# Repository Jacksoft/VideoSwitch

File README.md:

# VideoSwitch
VideoSwitch sources (PIC + Schematic)
This project is a VideoSwitch for retro devices (that uses SCART/Composite) and is based on a mainboard composed by a PIC microcontroller, a main switch/selector and eight multiplexer, and a daughterboard (to be designed) to add eight more ports (up to two for a total of 24 inputs, not guaranteed until I'll produce a prototype for the right tests).
On the mainboard can be connected an 8x2 LCD character display (or biggher by modifying the firmware), two buttons for the input port selection and an IR receiver (not implemented yet firmware side, need to write the NEC IR library).
The firmware is in MikroBASIC (yes, I'm lazy and this language isn't the best for microcontrollers, I know).
Find out more on http://blog.jacksoftlabs.com/digital-video-switch-for-retro-devices/

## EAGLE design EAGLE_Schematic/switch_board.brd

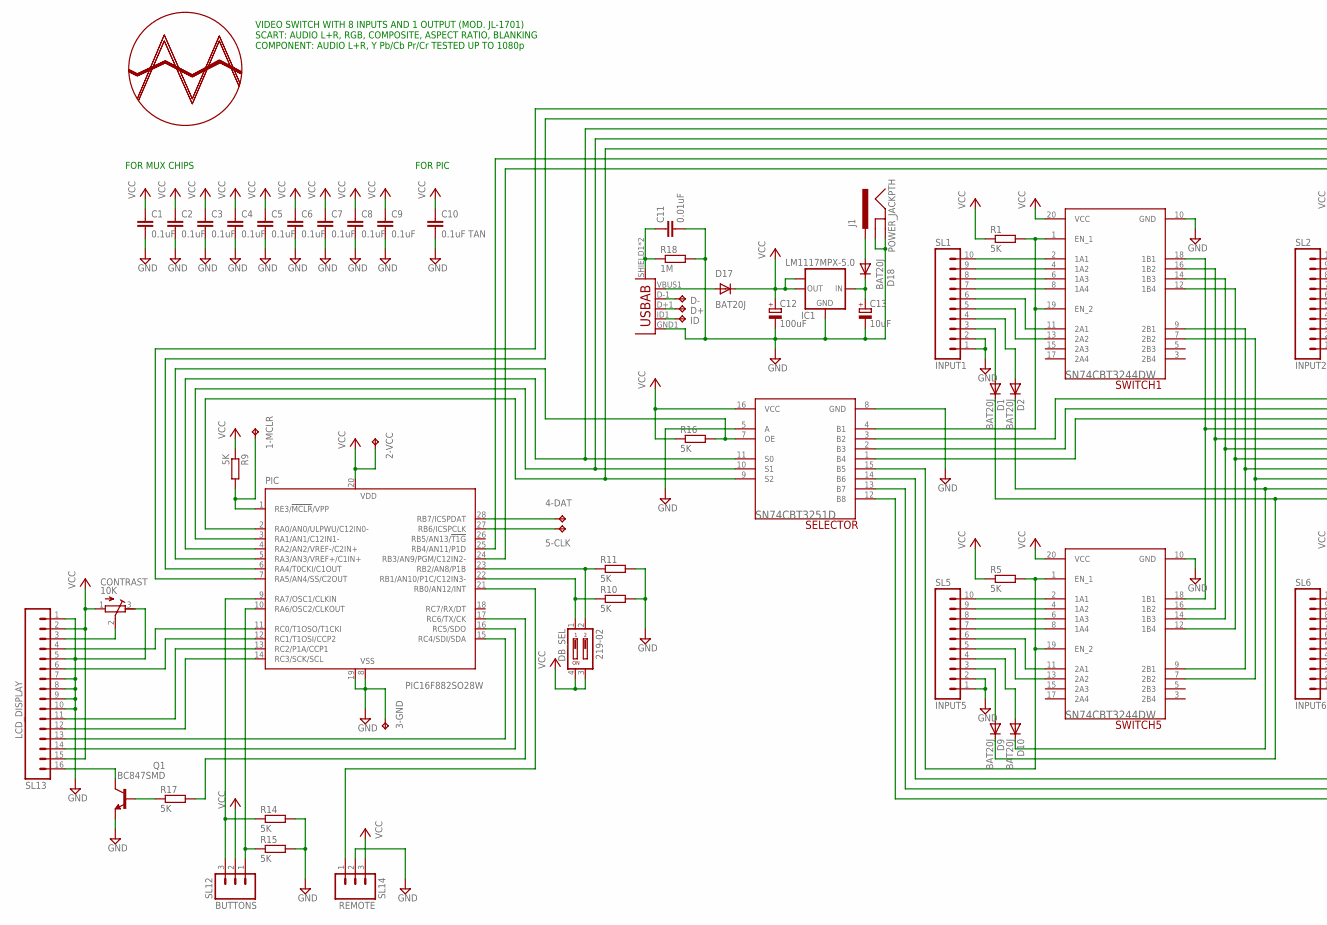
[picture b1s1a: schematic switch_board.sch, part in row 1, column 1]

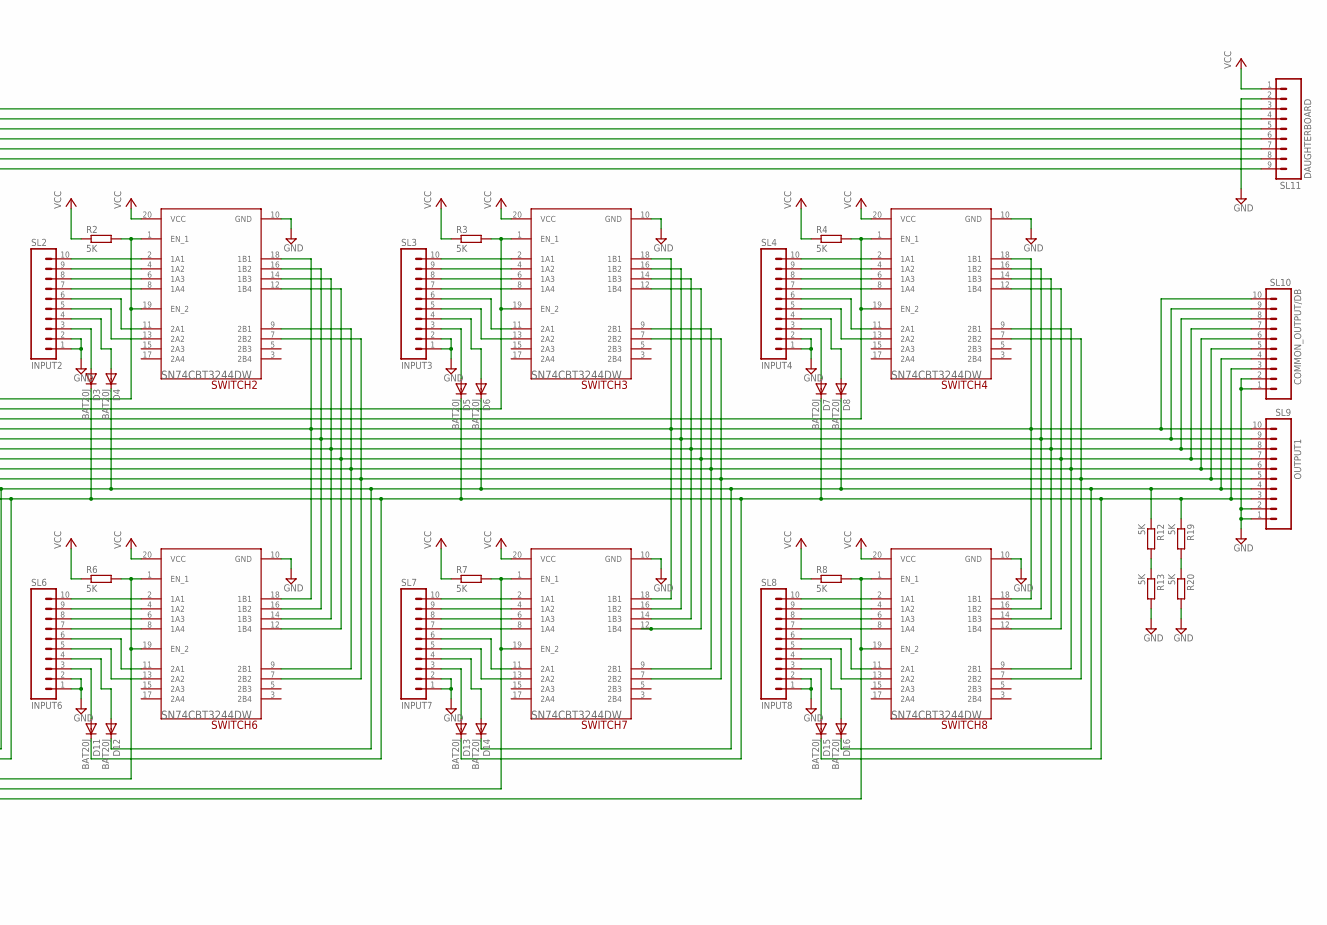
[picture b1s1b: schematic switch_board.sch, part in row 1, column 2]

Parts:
1-MCLR, 2-VCC, 3-GND, 4-DAT, 5-CLK: TPB1,27; B1,27
C1, C2, C3, C4, C5, C6, C7, C8, C9: 0.1uF; C0603
C10: 0.1uF TAN; C3216
C11: 0.01uF; C0603
C12: 100uF; 153CLV-0405
C13: 10uF; 153CLV-0405
CONTRAST: 10K; RTRIM3304W
D1, D2, D3, D4, D5, D6, D7, D8, D9, D10, D11, D12, D13, D14, D15, D16, D17, D18: BAT20J; SOD323-W
D+: TPTP06R; TP06R
D-: TPTP06R; TP06R
DB_SEL: 219-02; CTS-219-02
IC1: LM1117MPX-5.0; SOT223
ID: TPTP06R; TP06R
J1: POWER_JACKPTH; POWER_JACK_PTH
PIC: PIC16F882SO28W; 16F882
Q1: BC847SMD; SOT23
R1, R2, R3, R4, R5, R6, R7, R8, R9, R10, R11, R12, R13, R14, R15, R16, R17, R19, R20: 5K; R0603
R18: 1M; R0603
SELECTOR: SN74CBT3251D; SOIC127P1032X265-16N
SL1: INPUT1; 10P
SL2: INPUT2; 10P
SL3: INPUT3; 10P
SL4: INPUT4; 10P
SL5: INPUT5; 10P
SL6: INPUT6; 10P
SL7: INPUT7; 10P
SL8: INPUT8; 10P
SL9: OUTPUT1; 10P
SL10: COMMON_OUTPUT/DB; 10P
SL11: DAUGHTERBOARD; 09P
SL12: BUTTONS; 03P
SL13: LCD_DISPLAY; 16P
SL14: REMOTE; 03P
SWITCH1, SWITCH2, SWITCH3, SWITCH4, SWITCH5, SWITCH6, SWITCH7, SWITCH8: SN74CBT3244DW; SOIC127P1032X265-20N
U$1: JACKSOFTLABS-LOGOLONGTEXT; LOGO-LONGTEXT
USB: USB_POWER; USB-MICRO-SMD

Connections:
GND: 3-GND.TP, C1.2, C2.2, C3.2, C4.2, C5.2, C6.2, C7.2, C8.2, C9.2, C10.2, C11.2, C12.-, C13.-, CONTRAST.3 (E), IC1.1 (GND), J1.GND, J1.GNDBREAK, PIC.8 (VSS), PIC.19 (VSS), Q1.2 (E), R10.2, R11.2, R13.2, R14.2, R15.2, R18.2, R20.2, SELECTOR.5 (A), SELECTOR.8 (GND), SL1.1, SL1.2, SL2.1, SL2.2, SL3.1, SL3.2, SL4.1, SL4.2, SL5.1, SL5.2, SL6.1, SL6.2, SL7.1, SL7.2, SL8.1, SL8.2, SL9.1, SL9.2, SL10.1, SL10.2, SL11.2, SL13.1, SL13.5, SL13.7, SL13.8, SL13.9, SL13.10, SL14.2, SWITCH1.10 (GND), SWITCH2.10 (GND), SWITCH3.10 (GND), SWITCH4.10 (GND), SWITCH5.10 (GND), SWITCH6.10 (GND), SWITCH7.10 (GND), SWITCH8.10 (GND), USB.GND1 (GND)
unnamed: SL1.10, SWITCH1.2 (1A1)
unnamed: SL1.9, SWITCH1.4 (1A2)
unnamed: SL1.8, SWITCH1.6 (1A3)
unnamed: SL1.7, SWITCH1.8 (1A4)
unnamed: SL1.6, SWITCH1.11 (2A1)
unnamed: SL1.5, SWITCH1.13 (2A2)
unnamed: D2.A, SL1.4
unnamed: D1.A, SL1.3
unnamed: R1.2, SELECTOR.4 (B1), SWITCH1.1 (EN_1), SWITCH1.19 (EN_2)
unnamed: SL2.10, SWITCH2.2 (1A1)
unnamed: SL2.9, SWITCH2.4 (1A2)
unnamed: SL2.8, SWITCH2.6 (1A3)
unnamed: SL2.7, SWITCH2.8 (1A4)
unnamed: SL2.6, SWITCH2.11 (2A1)
unnamed: SL2.5, SWITCH2.13 (2A2)
unnamed: D4.A, SL2.4
unnamed: D3.A, SL2.3
unnamed: R2.2, SELECTOR.3 (B2), SWITCH2.1 (EN_1), SWITCH2.19 (EN_2)
unnamed: SL3.10, SWITCH3.2 (1A1)
unnamed: SL3.9, SWITCH3.4 (1A2)
unnamed: SL3.8, SWITCH3.6 (1A3)
unnamed: SL3.7, SWITCH3.8 (1A4)
unnamed: SL3.6, SWITCH3.11 (2A1)
unnamed: SL3.5, SWITCH3.13 (2A2)
unnamed: D6.A, SL3.4
unnamed: D5.A, SL3.3
unnamed: R3.2, SELECTOR.2 (B3), SWITCH3.1 (EN_1), SWITCH3.19 (EN_2)
unnamed: SL4.10, SWITCH4.2 (1A1)
unnamed: SL4.9, SWITCH4.4 (1A2)
unnamed: SL4.8, SWITCH4.6 (1A3)
unnamed: SL4.7, SWITCH4.8 (1A4)
unnamed: SL4.6, SWITCH4.11 (2A1)
unnamed: SL4.5, SWITCH4.13 (2A2)
unnamed: D8.A, SL4.4
unnamed: D7.A, SL4.3
unnamed: R4.2, SELECTOR.1 (B4), SWITCH4.1 (EN_1), SWITCH4.19 (EN_2)
unnamed: SL9.10, SL10.10, SWITCH1.18 (1B1), SWITCH2.18 (1B1), SWITCH3.18 (1B1), SWITCH4.18 (1B1), SWITCH5.18 (1B1), SWITCH6.18 (1B1), SWITCH7.18 (1B1), SWITCH8.18 (1B1)
unnamed: SL9.9, SL10.9, SWITCH1.16 (1B2), SWITCH2.16 (1B2), SWITCH3.16 (1B2), SWITCH4.16 (1B2), SWITCH5.16 (1B2), SWITCH6.16 (1B2), SWITCH7.16 (1B2), SWITCH8.16 (1B2)
unnamed: PIC.11 (RC0/T1OSO/T1CKI), SL13.4
unnamed: PIC.12 (RC1/T1OSI/CCP2), SL13.6
unnamed: PIC.13 (RC2/P1A/CCP1), SL13.11
unnamed: DB_SEL.1, PIC.22 (RB1/AN10/P1C/C12IN3-), R10.1
unnamed: PIC.14 (RC3/SCK/SCL), SL13.12
unnamed: CONTRAST.2 (S), SL13.3
unnamed: SL5.10, SWITCH5.2 (1A1)
unnamed: SL5.9, SWITCH5.4 (1A2)
unnamed: SL5.8, SWITCH5.6 (1A3)
unnamed: SL5.7, SWITCH5.8 (1A4)
unnamed: SL5.6, SWITCH5.11 (2A1)
unnamed: SL5.5, SWITCH5.13 (2A2)
unnamed: D10.A, SL5.4
unnamed: D9.A, SL5.3
unnamed: R5.2, SELECTOR.15 (B5), SWITCH5.1 (EN_1), SWITCH5.19 (EN_2)
unnamed: SL6.10, SWITCH6.2 (1A1)
unnamed: SL6.9, SWITCH6.4 (1A2)
unnamed: SL6.8, SWITCH6.6 (1A3)
unnamed: SL6.7, SWITCH6.8 (1A4)
unnamed: SL6.6, SWITCH6.11 (2A1)
unnamed: SL6.5, SWITCH6.13 (2A2)
unnamed: D12.A, SL6.4
unnamed: D11.A, SL6.3
unnamed: R6.2, SELECTOR.14 (B6), SWITCH6.1 (EN_1), SWITCH6.19 (EN_2)
unnamed: SL7.10, SWITCH7.2 (1A1)
unnamed: SL7.9, SWITCH7.4 (1A2)
unnamed: SL7.8, SWITCH7.6 (1A3)
unnamed: SL7.7, SWITCH7.8 (1A4)
unnamed: SL7.6, SWITCH7.11 (2A1)
unnamed: SL7.5, SWITCH7.13 (2A2)
unnamed: D14.A, SL7.4
unnamed: D13.A, SL7.3
unnamed: R7.2, SELECTOR.13 (B7), SWITCH7.1 (EN_1), SWITCH7.19 (EN_2)
unnamed: SL8.10, SWITCH8.2 (1A1)
unnamed: SL8.9, SWITCH8.4 (1A2)
unnamed: SL8.8, SWITCH8.6 (1A3)
unnamed: SL8.7, SWITCH8.8 (1A4)
unnamed: SL8.6, SWITCH8.11 (2A1)
unnamed: SL8.5, SWITCH8.13 (2A2)
unnamed: D16.A, SL8.4
unnamed: D15.A, SL8.3
unnamed: R8.2, SELECTOR.12 (B8), SWITCH8.1 (EN_1), SWITCH8.19 (EN_2)
unnamed: DB_SEL.2, PIC.23 (RB2/AN8/P1B), R11.1
unnamed: 1-MCLR.TP, PIC.1 (RE3/!MCLR!/VPP), R9.2
unnamed: PIC.5 (RA3/AN3/VREF+/C1IN+), R16.2, SELECTOR.7 (OE)
unnamed: C11.1, R18.1, USB.SHIELD1 (SHIELD), USB.SHIELD2 (SHIELD)
unnamed: PIC.4 (RA2/AN2/VREF-/C2IN+), SELECTOR.11 (S0), SL11.5
unnamed: PIC.3 (RA1/AN1/C12IN1-), SELECTOR.10 (S1), SL11.6
unnamed: PIC.2 (RA0/AN0/ULPWU/C12IN0-), SELECTOR.9 (S2), SL11.7
unnamed: PIC.6 (RA4/T0CKI/C1OUT), SL11.4
unnamed: 4-DAT.TP, PIC.28 (RB7/ICSPDAT)
unnamed: 5-CLK.TP, PIC.27 (RB6/ICSPCLK)
unnamed: PIC.7 (RA5/AN4/SS/C2OUT), SL11.3
unnamed: Q1.3 (C), SL13.16
unnamed: Q1.1 (B), R17.1
unnamed: D17.A, USB.VBUS1 (VBUS)
unnamed: PIC.21 (RB0/AN12/INT), SL14.1
unnamed: PIC.15 (RC4/SDI/SDA), SL13.13
unnamed: PIC.16 (RC5/SDO), SL13.14
unnamed: PIC.17 (RC6/TX/CK), R17.2
unnamed: C13.+, D18.C, IC1.3 (IN)
unnamed: PIC.10 (RA6/OSC2/CLKOUT), R15.1, SL12.1
unnamed: PIC.9 (RA7/OSC1/CLKIN), R14.1, SL12.3
unnamed: D1.C, D3.C, D5.C, D7.C, D9.C, D11.C, D13.C, D15.C, R19.1, SL9.3, SL10.3
unnamed: D2.C, D4.C, D6.C, D8.C, D10.C, D12.C, D14.C, D16.C, R12.1, SL9.4, SL10.4
unnamed: SL9.5, SL10.5, SWITCH1.7 (2B2), SWITCH2.7 (2B2), SWITCH3.7 (2B2), SWITCH4.7 (2B2), SWITCH5.7 (2B2), SWITCH6.7 (2B2), SWITCH7.7 (2B2), SWITCH8.7 (2B2)
unnamed: SL9.6, SL10.6, SWITCH1.9 (2B1), SWITCH2.9 (2B1), SWITCH3.9 (2B1), SWITCH4.9 (2B1), SWITCH5.9 (2B1), SWITCH6.9 (2B1), SWITCH7.9 (2B1), SWITCH8.9 (2B1)
unnamed: SL9.7, SL10.7, SWITCH1.12 (1B4), SWITCH2.12 (1B4), SWITCH3.12 (1B4), SWITCH4.12 (1B4), SWITCH5.12 (1B4), SWITCH6.12 (1B4), SWITCH7.12 (1B4), SWITCH8.12 (1B4)
unnamed: SL9.8, SL10.8, SWITCH1.14 (1B3), SWITCH2.14 (1B3), SWITCH3.14 (1B3), SWITCH4.14 (1B3), SWITCH5.14 (1B3), SWITCH6.14 (1B3), SWITCH7.14 (1B3), SWITCH8.14 (1B3)
unnamed: D18.A, J1.PWR
unnamed: D-.TP, USB.D-1 (D-)
unnamed: D+.TP, USB.D+1 (D+)
unnamed: ID.TP, USB.ID1 (USBID)
unnamed: R12.2, R13.1
unnamed: R19.2, R20.1
unnamed: PIC.25 (RB4/AN11/P1D), SL11.8
unnamed: PIC.24 (RB3/AN9/PGM/C12IN2-), SL11.9
VCC: 2-VCC.TP, C1.1, C2.1, C3.1, C4.1, C5.1, C6.1, C7.1, C8.1, C9.1, C10.1, C12.+, CONTRAST.1 (A), D17.C, DB_SEL.3, DB_SEL.4, IC1.2 (OUT), IC1.TAB (OUT1), PIC.20 (VDD), R1.1, R2.1, R3.1, R4.1, R5.1, R6.1, R7.1, R8.1, R9.1, R16.1, SELECTOR.16 (VCC), SL11.1, SL12.2, SL13.2, SL13.15, SL14.3, SWITCH1.20 (VCC), SWITCH2.20 (VCC), SWITCH3.20 (VCC), SWITCH4.20 (VCC), SWITCH5.20 (VCC), SWITCH6.20 (VCC), SWITCH7.20 (VCC), SWITCH8.20 (VCC)

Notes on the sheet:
FOR MUX CHIPS
FOR PIC
VIDEO SWITCH WITH 8 INPUTS AND 1 OUTPUT (MOD. JL-1701) SCART: AUDIO L+R, RGB, COMPOSITE, ASPECT RATIO, BLANKING COMPONENT: AUDIO L+R, Y Pb/Cb Pr/Cr TESTED UP TO 1080p

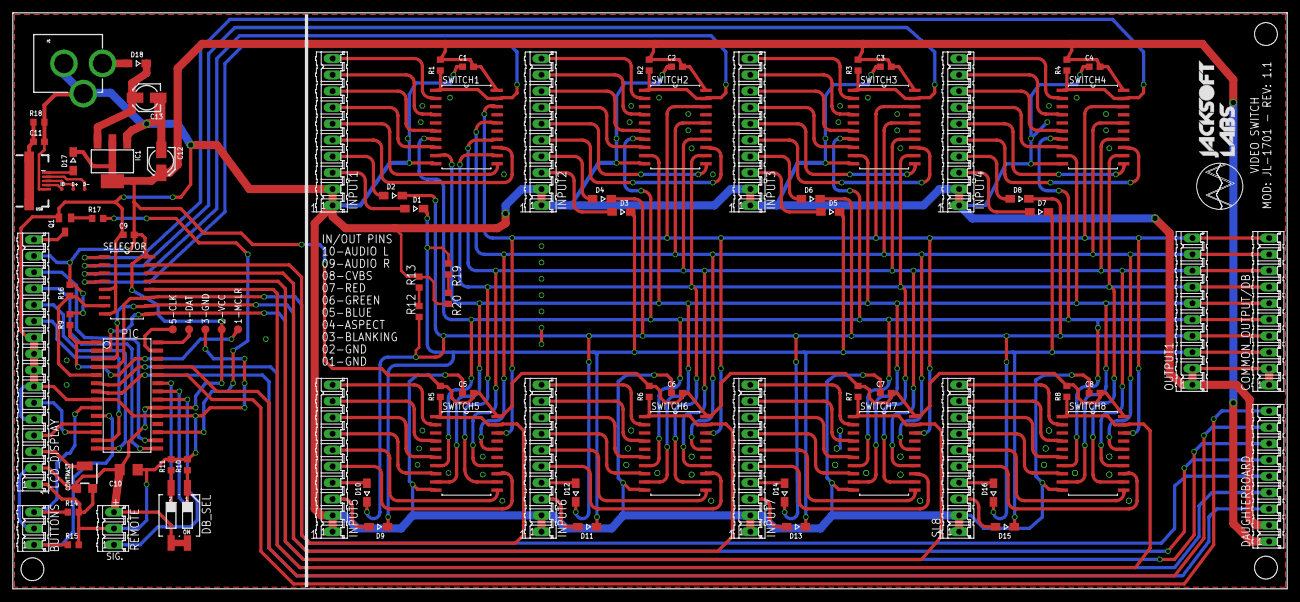
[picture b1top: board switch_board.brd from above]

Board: 2 copper layers, 198.4 x 89.7 mm, 90 parts (0 on the bottom side), 117 nets.

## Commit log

2018-10-28 Update LICENSE.md
    Creative Commons - Attribution - ShareAlike 3.0
2018-10-28 Add files via upload
    PIC source code with HEX
2018-10-28 EAGLE Schematic Files
2018-10-28 Renaming Resources
2018-10-28 PIC FW sourcecode
    PIC FW sourcecode + HEX in MikroBASIC
2018-10-28 Create README.md
    Find out what this project is...
2018-10-28 Fixed a text

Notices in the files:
parts and their libraries:
SparkFun-Connectors: Licensing: Creative Commons ShareAlike 4.0 International - https://creativecommons.org/licenses/by-sa/4.0
